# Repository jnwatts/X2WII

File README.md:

# X2WII
Adapt Gamecube/N64 controllers as Wii-mote extensions

My own implementation of [Raphaël Assénat][http://www.raphnet.net/contact/contact_en.php]'s [Extenmote][http://www.raphnet.net/electronique/extenmote/index_en.php].

#Licenses
All sofware and hardware found within this repository is released under version 3 of the [GPL][http://www.gnu.org/licenses/gpl-3.0.txt].

PDFs found in the Docs folder are copywrite their original owners and to the best of my knowledge may be shared un-modified.

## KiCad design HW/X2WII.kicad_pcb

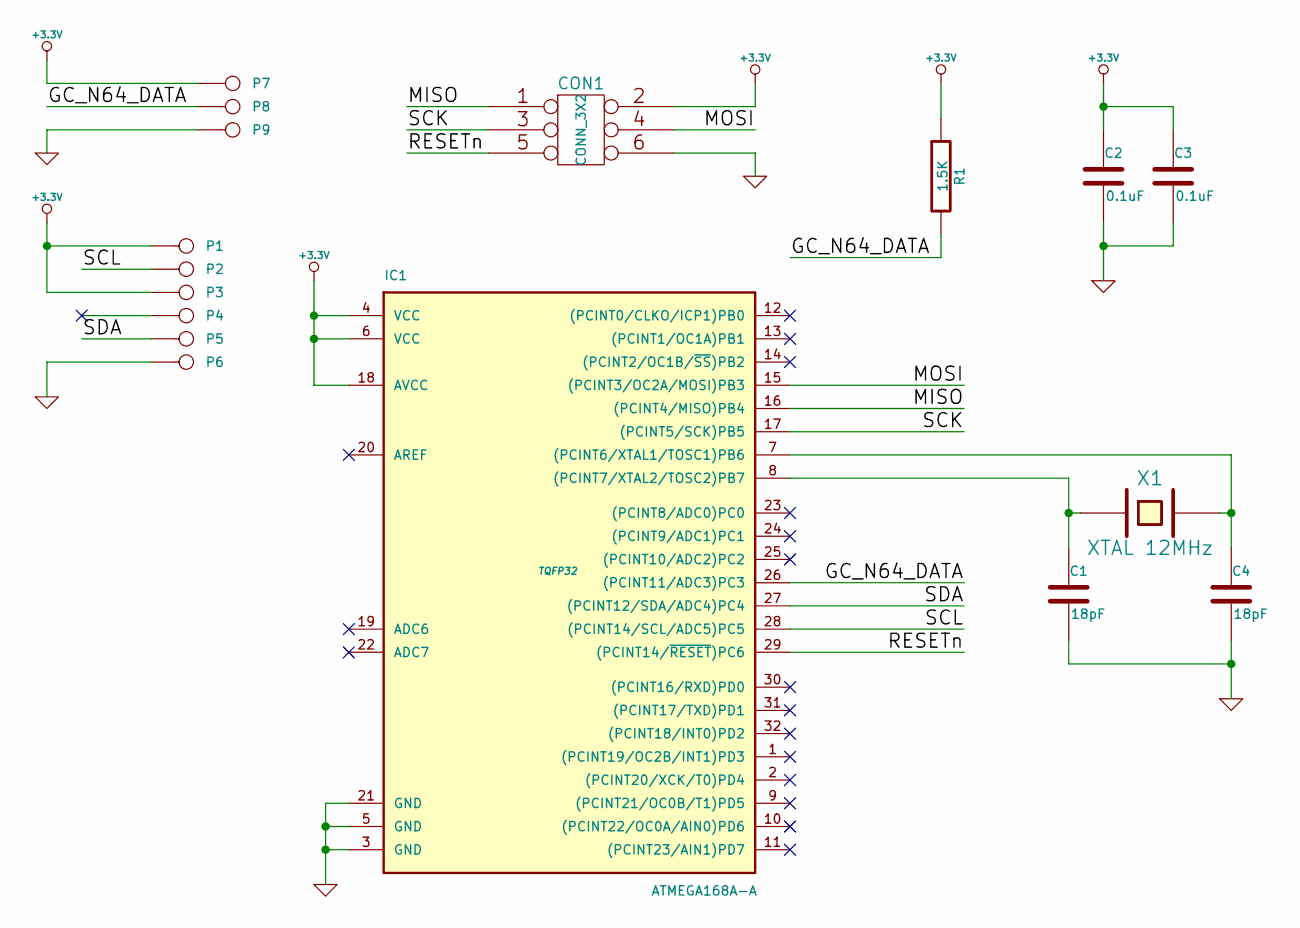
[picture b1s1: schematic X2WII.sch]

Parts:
C1, C4: 18pF
C2, C3: 0.1uF
CON1: CONN_3X2
IC1: ATMEGA168A-A; TQFP32
P1, P2, P3, P4, P5, P6, P7, P8, P9: CONN_1
R1: 1.5K
X1: XTAL 12MHz

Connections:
+3.3V: C2.1, C3.1, CON1.2, IC1.4 (VCC), IC1.6 (VCC), IC1.18 (AVCC), P1.1, P3.1, P7.1, R1.1
/GC_N64_DATA: IC1.26 ((PCINT11/ADC3)PC3), P8.1, R1.2
/MISO: CON1.1, IC1.16 ((PCINT4/MISO)PB4)
/MOSI: CON1.4, IC1.15 ((PCINT3/OC2A/MOSI)PB3)
/RESETn: CON1.5, IC1.29 ((PCINT14/~RESET~)PC6)
/SCK: CON1.3, IC1.17 ((PCINT5/SCK)PB5)
/SCL: IC1.28 ((PCINT14/SCL/ADC5)PC5), P2.1
/SDA: IC1.27 ((PCINT12/SDA/ADC4)PC4), P5.1
GND: C1.2, C2.2, C3.2, C4.2, CON1.6, IC1.3 (GND), IC1.5 (GND), IC1.21 (GND), P6.1, P9.1
unnamed: C4.1, IC1.7 ((PCINT6/XTAL1/TOSC1)PB6), X1.2
unnamed: C1.1, IC1.8 ((PCINT7/XTAL2/TOSC2)PB7), X1.1

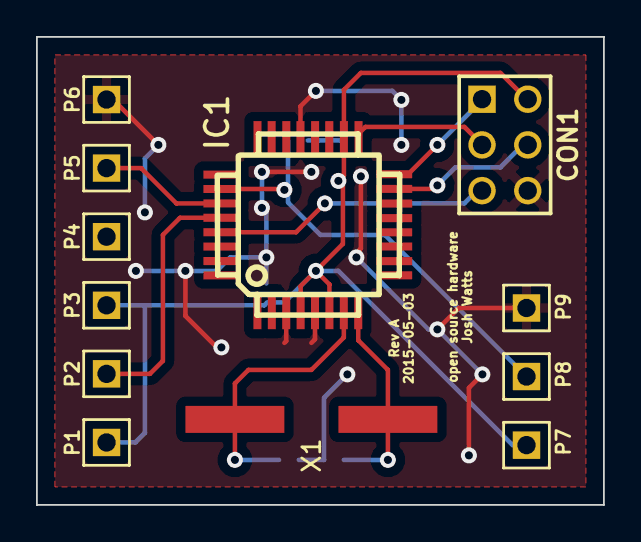
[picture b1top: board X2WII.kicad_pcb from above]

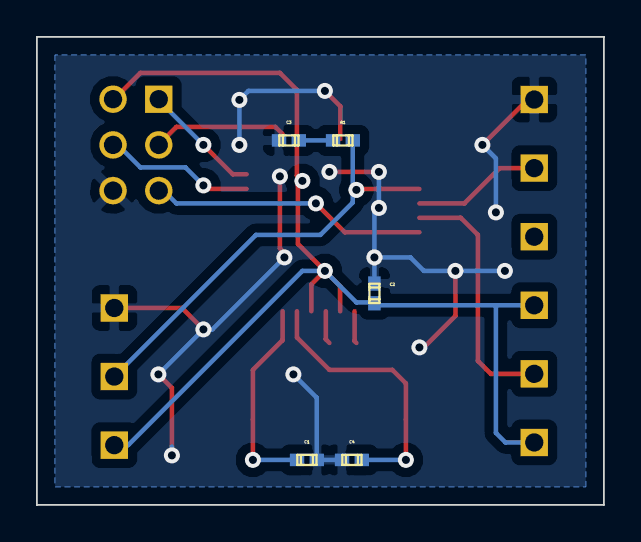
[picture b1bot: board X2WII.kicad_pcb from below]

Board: 2 copper layers, 31.5 x 26.0 mm, 17 parts (5 on the bottom side), 11 nets.

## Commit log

2015-05-15 Add SW folder, from extenmote-1.9.7.tar.gz (sha1: 64821ca3ca6409671b4b65d9664a1e5b004dce34)
2015-05-15 Renamed from GC2WII to X2WII
2015-05-15 Add Rev A HW
2015-05-15 Create objs dir if missing
2015-05-15 SW: Ignore objs*, *.elf, *.hex and *.map
2015-05-15 Add Makefile to build firmware and flash board
